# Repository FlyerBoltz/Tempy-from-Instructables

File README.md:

# Tempy-from-Instructables
Tempy- An Arduino Based Cute temprature controlled wall decoration smiley.

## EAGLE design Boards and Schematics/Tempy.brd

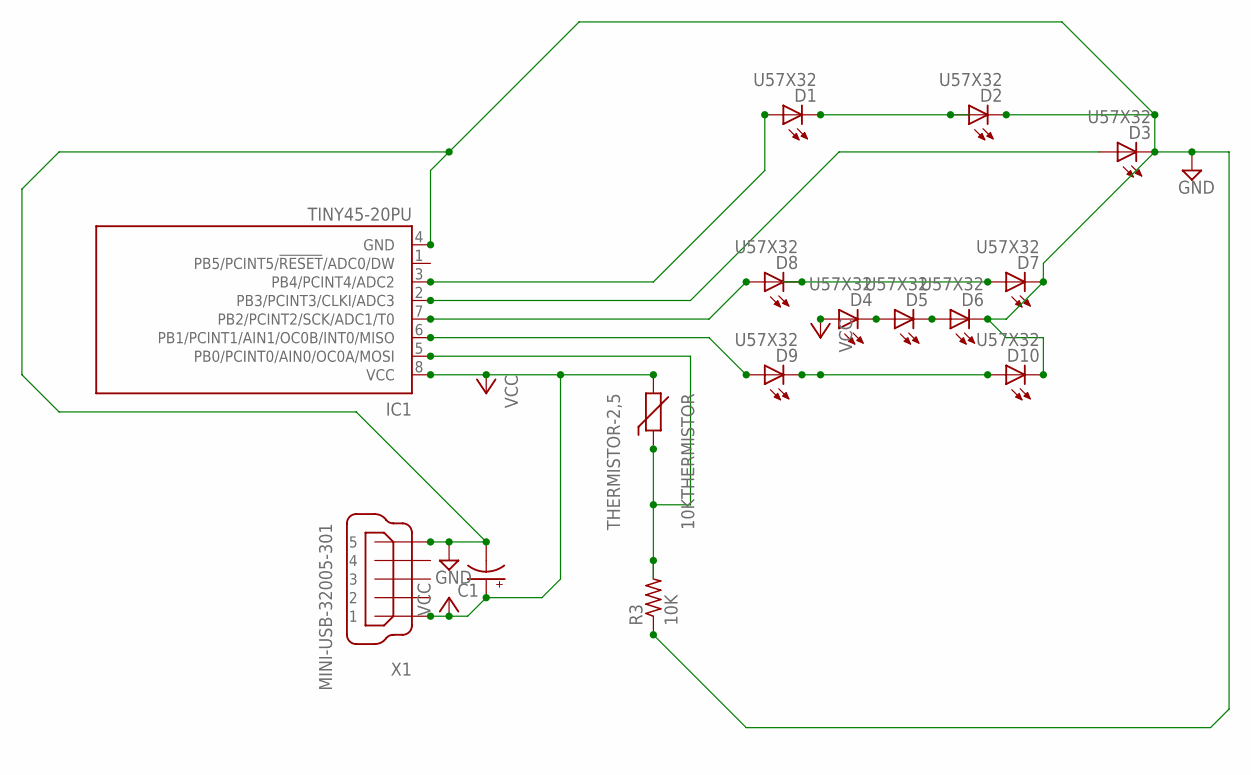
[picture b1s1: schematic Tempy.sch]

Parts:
10KTHERMISTOR: THERMISTOR-2,5; RS-2,5
C1: CPOL-USE5-4; E5-4
D1, D2, D3, D4, D5, D6, D7, D8, D9, D10: U57X32
IC1: TINY45-20PU; DIL08
R3: 10K; 0204/7
X1: MINI-USB-32005-301; 32005-301

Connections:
GND: C1.-, D2.K (C), D3.K (C), D6.K (C), D7.K (C), D10.K (C), IC1.4 (GND), R3.1, X1.5
unnamed: D4.K (C), D5.A
unnamed: D5.K (C), D6.A
unnamed: D9.A, IC1.6 (PB1/PCINT1/AIN1/OC0B/INT0/MISO)
unnamed: D1.K (C), D2.A
unnamed: D8.A, IC1.7 (PB2/PCINT2/SCK/ADC1/T0)
unnamed: D7.A, D8.K (C)
unnamed: D9.K (C), D10.A
unnamed: D3.A, IC1.2 (PB3/PCINT3/CLKI/ADC3)
unnamed: D1.A, IC1.3 (PB4/PCINT4/ADC2)
unnamed: 10KTHERMISTOR.1, IC1.5 (PB0/PCINT0/AIN0/OC0A/MOSI), R3.2
VCC: 10KTHERMISTOR.2, C1.+, D4.A, IC1.8 (VCC), X1.1

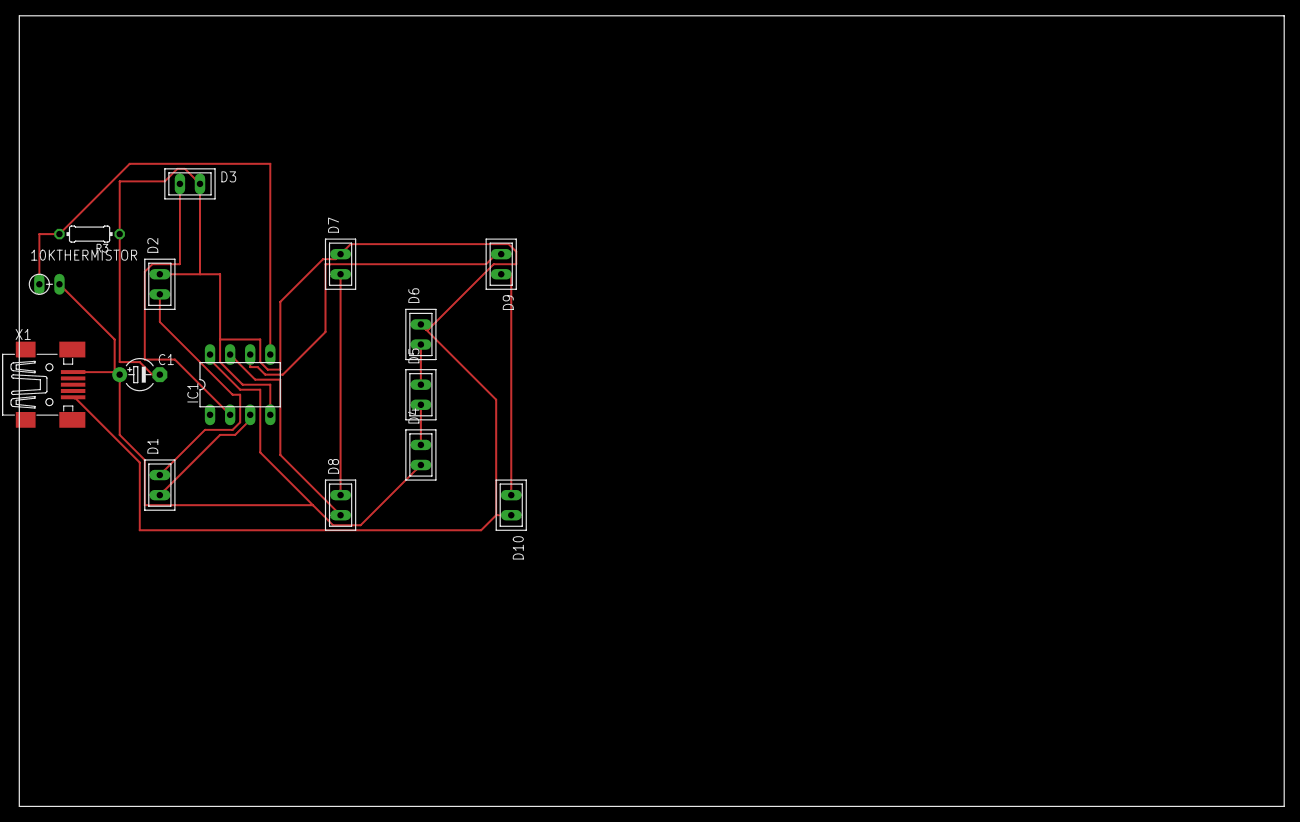
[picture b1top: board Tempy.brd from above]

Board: 2 copper layers, 160.0 x 100.0 mm, 15 parts (0 on the bottom side), 12 nets.

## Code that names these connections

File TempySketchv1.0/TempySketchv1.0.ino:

// **************************************************************************
// Sketch For Tempy- Temprature Controlled Smiley (On Instructables , By _Boltz_ Please don't change the credit.)Under Liscence CC-by-sa
// **************************************************************************
int mrr = 0.5; // Mood Refresh Rate , Changable, to tune the facial expression refresh rate
// **************************************************************************
#include <math.h>    //loads the more advanced math function
    int val;                //Create an integer variable
  double temp; 
  char mood; 
void setup() { 

}
 
double Thermister(int RawADC) {  //Function to perform the fancy math of the Steinhart-Hart equation
 double Temp;
 Temp = log(((10240000/RawADC) - 10000));
 Temp = 1 / (0.001129148 + (0.000234125 + (0.0000000876741 * Temp * Temp ))* Temp );
 Temp = Temp - 273.15;              // Convert Kelvin to Celsius
 return Temp;
}
 
void loop() 
{
 MoodRefresh();
 delay(mrr); 
}
void aoff()
{
digitalWrite(PB1,LOW);
digitalWrite(PB2,LOW);
digitalWrite(PB3,LOW);
}
void eyeblink()
{
  digitalWrite(PB4,HIGH);
  delay(random(0,3));
  digitalWrite(PB4,LOW);
  delay(200);
}
void meh()
{
  eyeblink();
  aoff();
}
void happy()
{
  aoff();
  digitalWrite(PB2,HIGH);
  eyeblink();
}
void sweat()
{
  aoff();
  eyeblink();
  digitalWrite(PB3,HIGH);
  digitalWrite(PB1,HIGH);
}

void shiver()
{
  aoff;
  digitalWrite(PB4,HIGH);
  digitalWrite(PB2,HIGH);
  digitalWrite(PB1,LOW);
  delay(150);
  digitalWrite(PB1,HIGH);
  digitalWrite(PB2,LOW);
  delay(150);
}
void MoodRefresh()
{
    val=analogRead(0);      //Read the analog port 0 and store the value in val
  temp=Thermister(val);   //Runs the fancy math on the raw analog value
  if(20<temp<25.4)
  {
    happy();
 }
 else if(25.5<temp<28)
 {
  meh();
 }
 else if(temp<20)
 {
  shiver();
 }
 else if(temp>28.001)
 {
  sweat();
 }
}

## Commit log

2016-05-06 Added files via upload
2016-05-06 Arduino Sketch File Upload
    Arduino Sketch File for tempy
2016-05-06 Circuit Image
